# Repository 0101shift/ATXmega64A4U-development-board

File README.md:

# ATXmega64A4U-development-board
A development board based on ATXmega64A4U controller. The design was halted due to non availability of JTAG probe (Atmel-ICE) at the time of development.

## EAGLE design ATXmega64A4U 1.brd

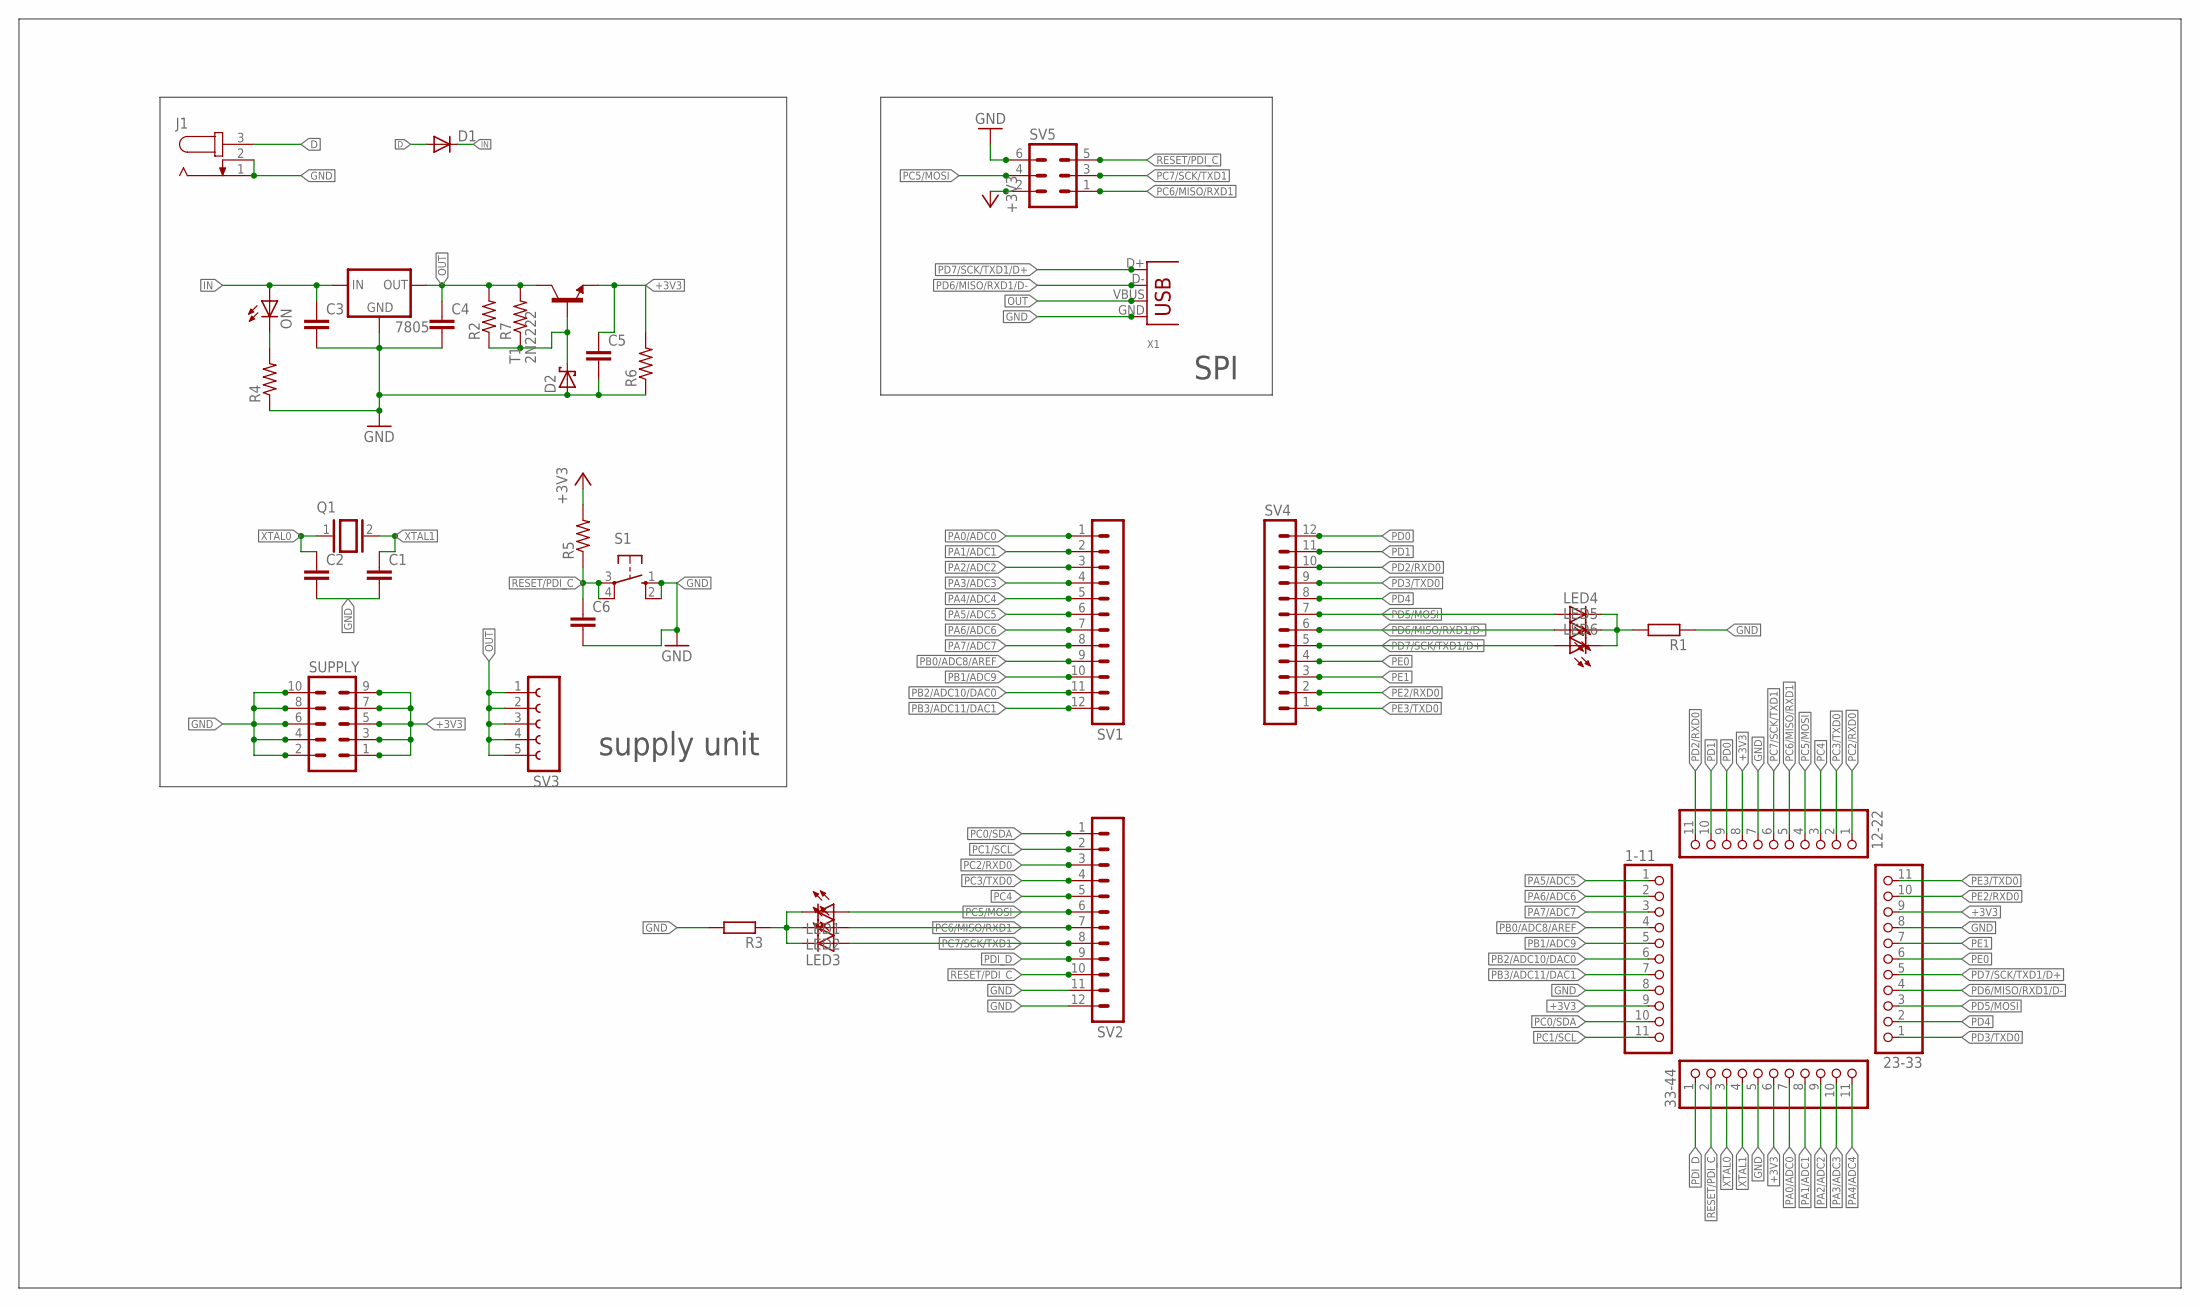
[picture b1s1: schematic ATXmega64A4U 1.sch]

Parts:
1-11, 12-22, 23-33, 33-44: PINHD-1X11/LONG; 1X11
7805: 78XXL
C1, C2, C3, C4, C5, C6: C-EU025-025X050; C025-025X050
D1: 1N4004; DO41-10
D2: SCHOTTKY-DIODEDO35-7; DO35-7
J1: JACK-PLUG0; SPC4077
LED1, LED2, LED3, LED4, LED5, LED6: LEDCHIPLED_0805; CHIPLED_0805
ON: LEDCHIP-LED0805; CHIP-LED0805
Q1: XTAL/S; QS
R1, R3: R-EU_0207/7; 0207/7
R2, R4, R5, R6, R7: R-US_0207/7; 0207/7
S1: 10-XX; B3F-10XX
SUPPLY: MA05-2
SV1, SV2, SV4: MA12-1
SV3: FE05-1
SV5: MA03-2
T1: 2N2222; TO18
X1: USB-B-H

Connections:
+3V3: 1-11.9, 12-22.8, 23-33.9, 33-44.6, C5.1, R5.2, R6.2, SUPPLY.1, SUPPLY.3, SUPPLY.5, SUPPLY.7, SUPPLY.9, SV5.2, T1.1 (E)
D: D1.A, J1.3
GND: 1-11.8, 12-22.7, 23-33.8, 33-44.5, 7805.GND, C1.2, C2.2, C3.2, C4.2, C5.2, C6.2, D2.A, J1.1, J1.2, R1.1, R3.2, R4.1, R6.1, S1.1 (S), S1.2 (S1), SUPPLY.2, SUPPLY.4, SUPPLY.6, SUPPLY.8, SUPPLY.10, SV2.11, SV2.12, SV5.6, X1.GND
IN: 7805.IN, C3.1, D1.C, ON.A
unnamed: ON.C, R4.2
unnamed: LED1.C, LED2.C, LED3.C, R3.1
unnamed: D2.C, R2.1, R7.1, T1.2 (B)
unnamed: LED4.C, LED5.C, LED6.C, R1.2
OUT: 7805.OUT, C4.1, R2.2, R7.2, SV3.1, SV3.2, SV3.3, SV3.4, SV3.5, T1.3 (C), X1.VBUS
PA0/ADC0: 33-44.7, SV1.1
PA1/ADC1: 33-44.8, SV1.2
PA2/ADC2: 33-44.9, SV1.3
PA3/ADC3: 33-44.10, SV1.4
PA4/ADC4: 33-44.11, SV1.5
PA5/ADC5: 1-11.1, SV1.6
PA6/ADC6: 1-11.2, SV1.7
PA7/ADC7: 1-11.3, SV1.8
PB0/ADC8/AREF: 1-11.4, SV1.9
PB1/ADC9: 1-11.5, SV1.10
PB2/ADC10/DAC0: 1-11.6, SV1.11
PB3/ADC11/DAC1: 1-11.7, SV1.12
PC0/SDA: 1-11.10, SV2.1
PC1/SCL: 1-11.11, SV2.2
PC2/RXD0: 12-22.1, SV2.3
PC3/TXD0: 12-22.2, SV2.4
PC4: 12-22.3, SV2.5
PC5/MOSI: 12-22.4, LED1.A, SV2.6, SV5.4
PC6/MISO/RXD1: 12-22.5, LED2.A, SV2.7, SV5.1
PC7/SCK/TXD1: 12-22.6, LED3.A, SV2.8, SV5.3
PD0: 12-22.9, SV4.12
PD1: 12-22.10, SV4.11
PD2/RXD0: 12-22.11, SV4.10
PD3/TXD0: 23-33.1, SV4.9
PD4: 23-33.2, SV4.8
PD5/MOSI: 23-33.3, LED4.A, SV4.7
PD6/MISO/RXD1/D-: 23-33.4, LED5.A, SV4.6, X1.D-
PD7/SCK/TXD1/D+: 23-33.5, LED6.A, SV4.5, X1.D+
PDI_D: 33-44.1, SV2.9
PE0: 23-33.6, SV4.4
PE1: 23-33.7, SV4.3
PE2/RXD0: 23-33.10, SV4.2
PE3/TXD0: 23-33.11, SV4.1
RESET/PDI_C: 33-44.2, C6.1, R5.1, S1.3, S1.4 (P1), SV2.10, SV5.5
XTAL0: 33-44.3, C2.1, Q1.1
XTAL1: 33-44.4, C1.1, Q1.2

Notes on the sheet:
supply unit
SPI

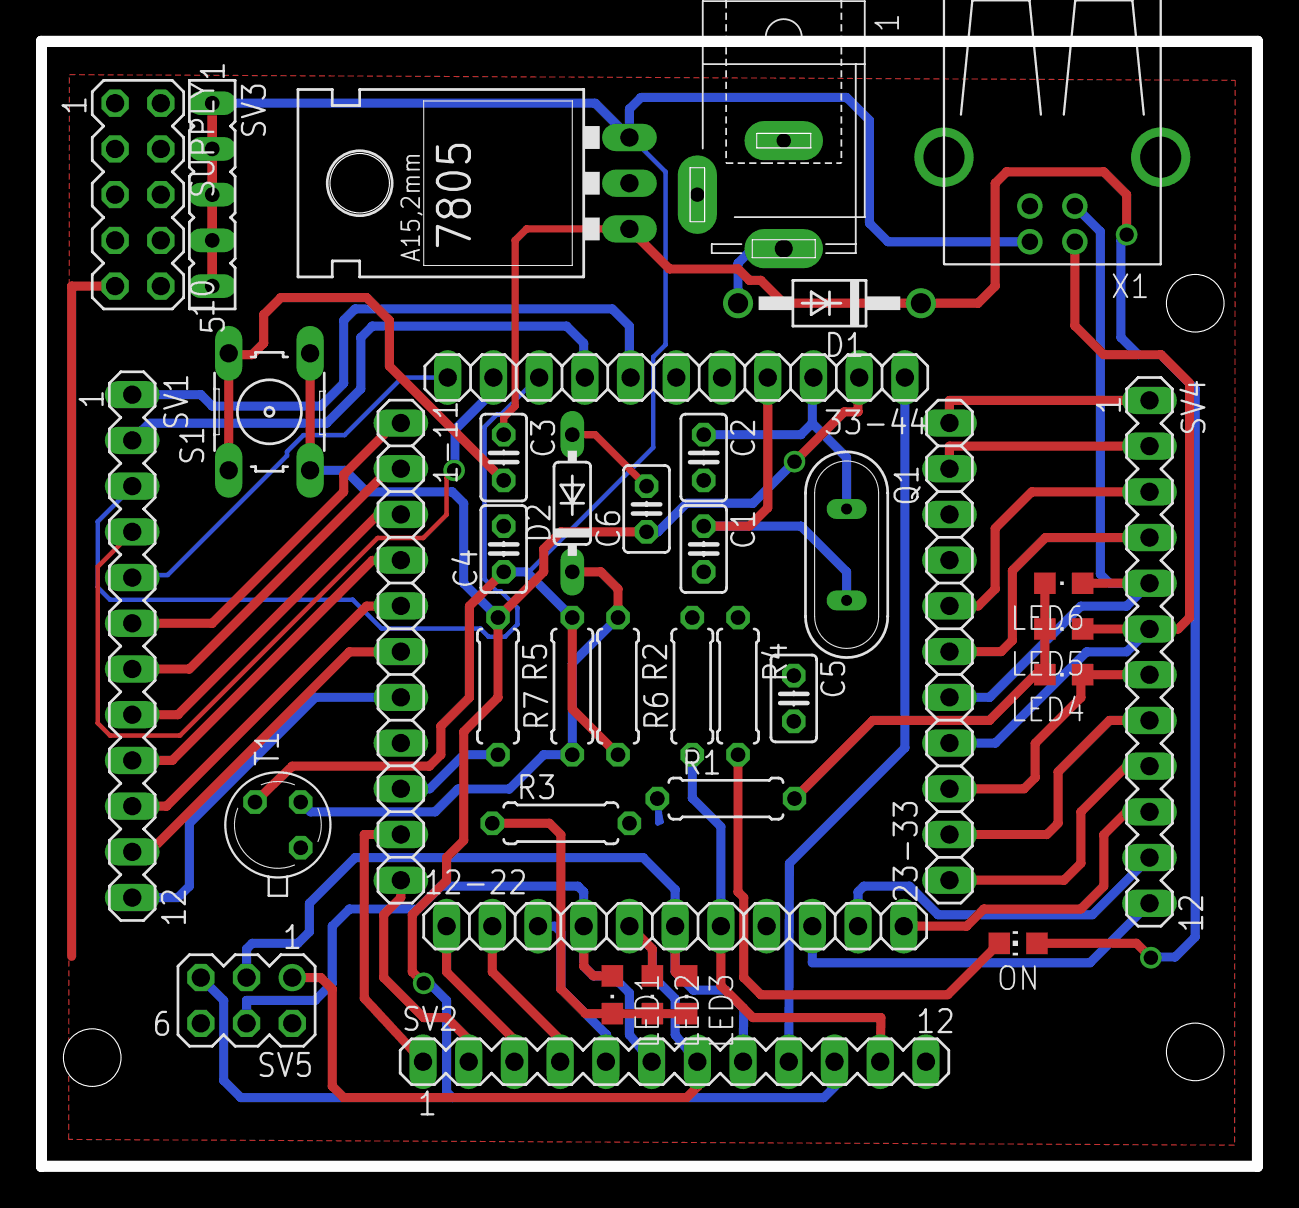
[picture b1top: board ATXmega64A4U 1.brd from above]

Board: 2 copper layers, 67.6 x 62.5 mm, 38 parts (0 on the bottom side), 45 nets.

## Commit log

2022-06-18 Add files via upload
    Added Project Design files
2022-06-18 Update README.md
    Added Images
